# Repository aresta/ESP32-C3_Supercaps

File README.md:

# ESP32-C3 Supercapacitor - Solar project
## ESP32-C3 weather station powered only with a supercapacitor and a Solar Panel

The ESP32-C3 is nice RISC-V microcontroller with relatively low power consumption.  

This project is a proof of concept on how to run a system like this, with regular wifi connection, without batteries. Just two small supercapacitors of 5F each, and a small solar panel (8 x 6 cms). It doesn't depend on any gateway in house, as it can directy connect to the internet to send the data.

The setup and code is very simple. The microcontroller stays in deep sleep most of the time. It wakes up every 15 minutes to take the weather measurements from the BME280 sensor ( temperature, humidity, pressure) and the voltage of the supercap. 

The measures are stored in the RTC memory and are only sent via WIFI if the charge of the supercap is at 95% or after a defined number of hours. This way the system can run and survive almost 3 days without any sun.

### Breadboard circuit

### The schematic

### New improved version: with ESP32 module and without boost converter

For the new version I designed a simple PCB and replaced the ESP32-C3 dev board by the ESP8685 WROOM module. It's still ESP32-C3 but as a module soldered to the PCB.

I have a new solar panel with the same size but the nominal voltage is 5.5V.  This allows me to remove completely the boost converter and replace it by a schottky diode (D2), what is more effient; it starts pushing with any tiny current, and consumes almost nothing. 

The Schottky should be choosen with very low reverse leakage current, to minize current lost during the night.

A 5.6V zener diode (D3) is added, because when the supercaps are full the panel could go above 5.5V.  With this configuration the maximum voltage observed is around 5.3 V. 

All together the system is much more efficient, charges even when the sky is covered and the losses are very small.

### PCB

## Time schedule:

- Take one sample every 15 mins and send it via WIFI.
- During the night (when voltage is below 5V):
  - Samples every 15 mins
  - Only every 8 samples (2 hours), it connects to the WIFI and sends all samples
- If the supercap voltage is below 3.5V don't connect the WIFI and reduce sample period to 30 minutes.

With this setup it survives more than 50 hours without any sun. When the sun is back in a couple of minutes the supercaps are fully charged and sends all pending samples.

In the RTC memory it can store about 1200 samples, so it can keep sampling and waitting until the sun is back and the supercap is charged again.

The system is running for more than 2 years now. Some example of the data collected:

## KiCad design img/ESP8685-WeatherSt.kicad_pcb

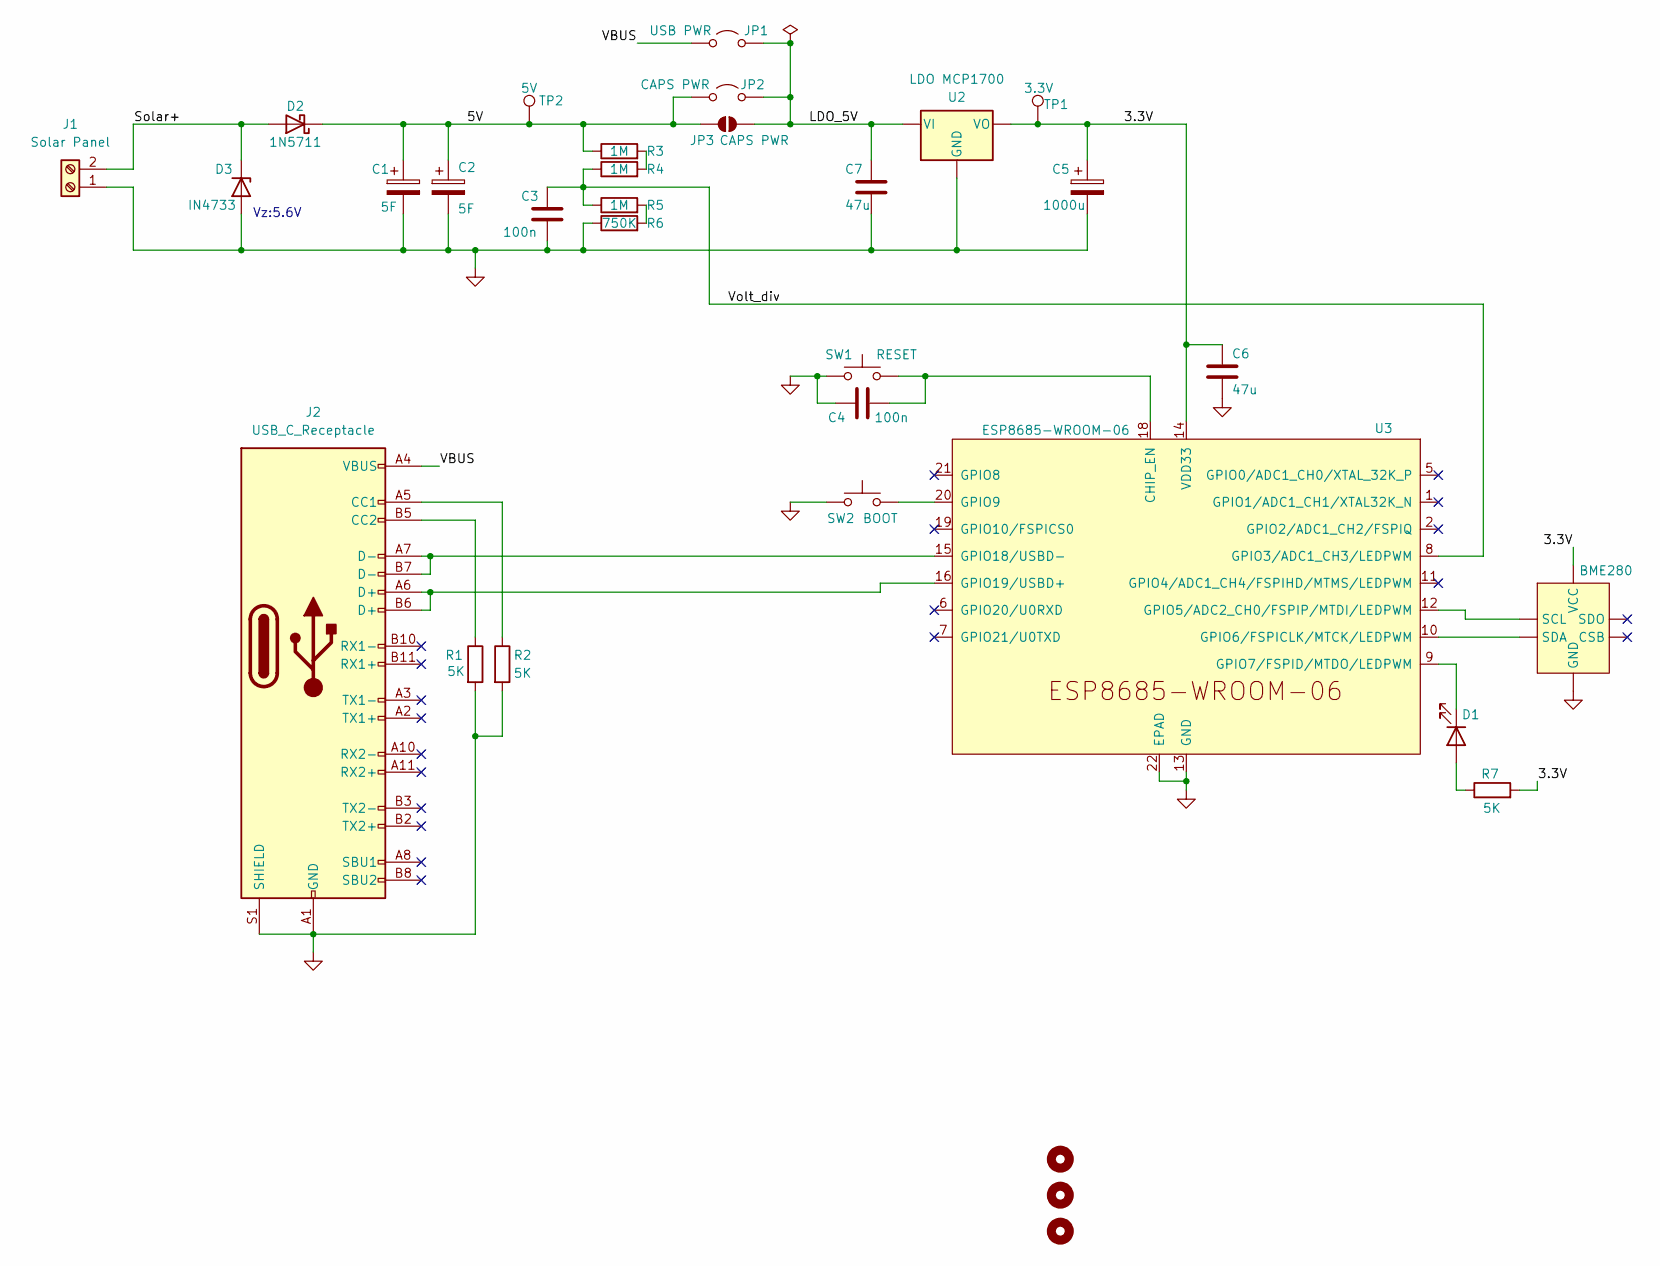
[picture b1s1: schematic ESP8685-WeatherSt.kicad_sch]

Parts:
BME1: BME280; PinHeader_1x06_P2.54mm_Horizontal
C1, C2: 5F; supercap
C3, C4: 100n; C_1206_3216Metric
C5: 1000u; C_Radial_D10.0mm_H16.0mm_P5.00mm
C6, C7: 47u; C_1206_3216Metric
D1: LED; LED_0805_2012Metric
D2: 1N5711; D_DO-35_SOD27_P7.62mm_Horizontal
D3: IN4733; D_DO-34_SOD68_P10.16mm_Horizontal
H1, H2, H3: MountingHole; MountingHole_2.2mm_M2_DIN965
J1: Solar Panel; TerminalBlock_Phoenix_MKDS-1,5-2-5.08_1x02_P5.08mm_Horizont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
J2: USB_C_Receptacle; USB_C_Receptacle_GCT_USB4105-xx-A_16P_TopMnt_Horizontal
JP1: USB PWR; PinHeader_1x02_P2.54mm_Vertical
JP2: CAPS PWR; PinHeader_1x02_P2.54mm_Vertical
JP3: CAPS PWR; SolderJumper-2_P1.3mm_Open_RoundedPad1.0x1.5mm
R1, R2, R7: 5K; R_1206_3216Metric
R3, R4, R5: 1M; R_1206_3216Metric
R6: 750K; R_1206_3216Metric
SW1: RESET; SW_Push_1P1T_NO_6x6mm_H9.5mm
SW2: BOOT; SW_Push_1P1T_NO_6x6mm_H9.5mm
TP1: 3.3V; TestPoint_Pad_D1.5mm
TP2: 5V; TestPoint_Pad_D1.5mm
U2: LDO MCP1700; TO-92_Inline
U3: ESP8685-WROOM-06

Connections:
/3.3V: BME1.1 (VCC), C5.1, C6.1, R7.2, TP1.1, U2.3 (VO), U3.14 (VDD33)
/5V: C1.1, C2.1, D2.1 (K), JP2.1 (A), JP3.1 (A), R3.1, TP2.1
/LDO_5V: C7.1, JP1.2 (B), JP2.2 (B), JP3.2 (B), U2.2 (VI)
/Solar+: D2.2 (A), D3.1 (K), J1.2
/VBUS: J2.A4 (VBUS), J2.A9 (VBUS), J2.B4 (VBUS), J2.B9 (VBUS), JP1.1 (A)
/Volt_div: C3.1, R4.1, R5.1, U3.8 (GPIO3/ADC1_CH3/LEDPWM)
GND: BME1.2 (GND), C1.2, C2.2, C3.2, C4.1, C5.2, C6.2, C7.2, D3.2 (A), J1.1, J2.A1 (GND), J2.A12 (GND), J2.B1 (GND), J2.B12 (GND), J2.S1 (SHIELD), R1.2, R2.2, R6.1, SW1.1, SW2.1, U2.1 (GND), U3.13 (GND), U3.22 (EPAD)
unnamed: BME1.3 (SCL), U3.12 (GPIO5/ADC2_CH0/FSPIP/MTDI/LEDPWM)
unnamed: BME1.4 (SDA), U3.10 (GPIO6/FSPICLK/MTCK/LEDPWM)
unnamed: D1.2 (A), R7.1
unnamed: D1.1 (K), U3.9 (GPIO7/FSPID/MTDO/LEDPWM)
unnamed: J2.A5 (CC1), R2.1
unnamed: J2.B5 (CC2), R1.1
unnamed: R3.2, R4.2
unnamed: R5.2, R6.2
unnamed: C4.2, SW1.2, U3.18 (CHIP_EN)
unnamed: SW2.2, U3.20 (GPIO9)
unnamed: J2.A7 (D-), J2.B7 (D-), U3.15 (GPIO18/USBD-)
unnamed: J2.A6 (D+), J2.B6 (D+), U3.16 (GPIO19/USBD+)

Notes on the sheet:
Vz:5.6V

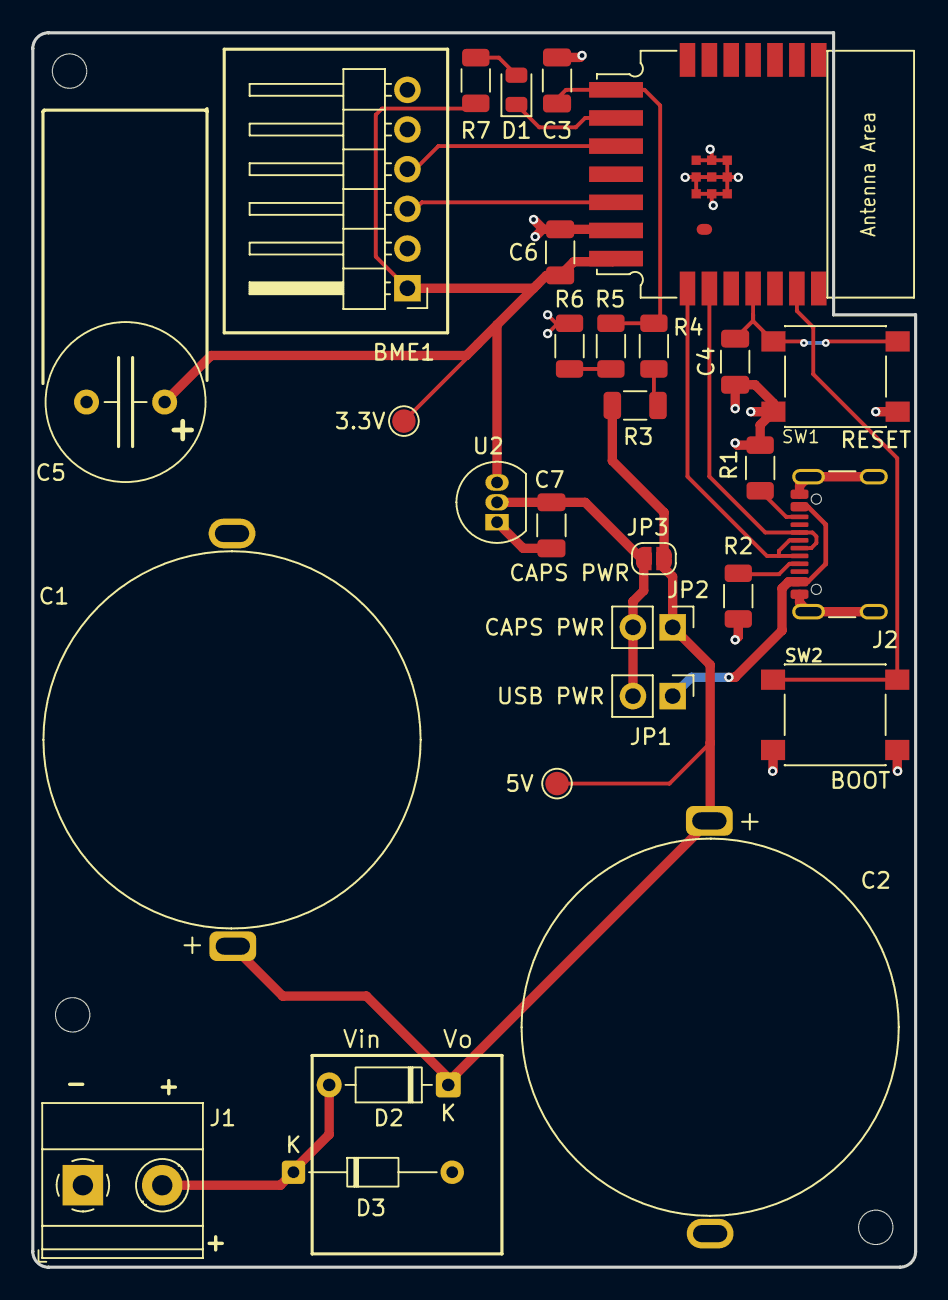
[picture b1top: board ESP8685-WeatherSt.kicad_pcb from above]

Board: 2 copper layers, 56.5 x 79.0 mm, 32 parts (0 on the bottom side), 19 nets.

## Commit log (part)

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2024-01-20 initial verstio
2024-04-06 Moved to esp8685 and new PCB
2024-11-15 Added new version
2024-11-15 plot added
2026-04-23 new version with schottky instead of boost
2026-05-08 when caps are full, send every 2nd time
